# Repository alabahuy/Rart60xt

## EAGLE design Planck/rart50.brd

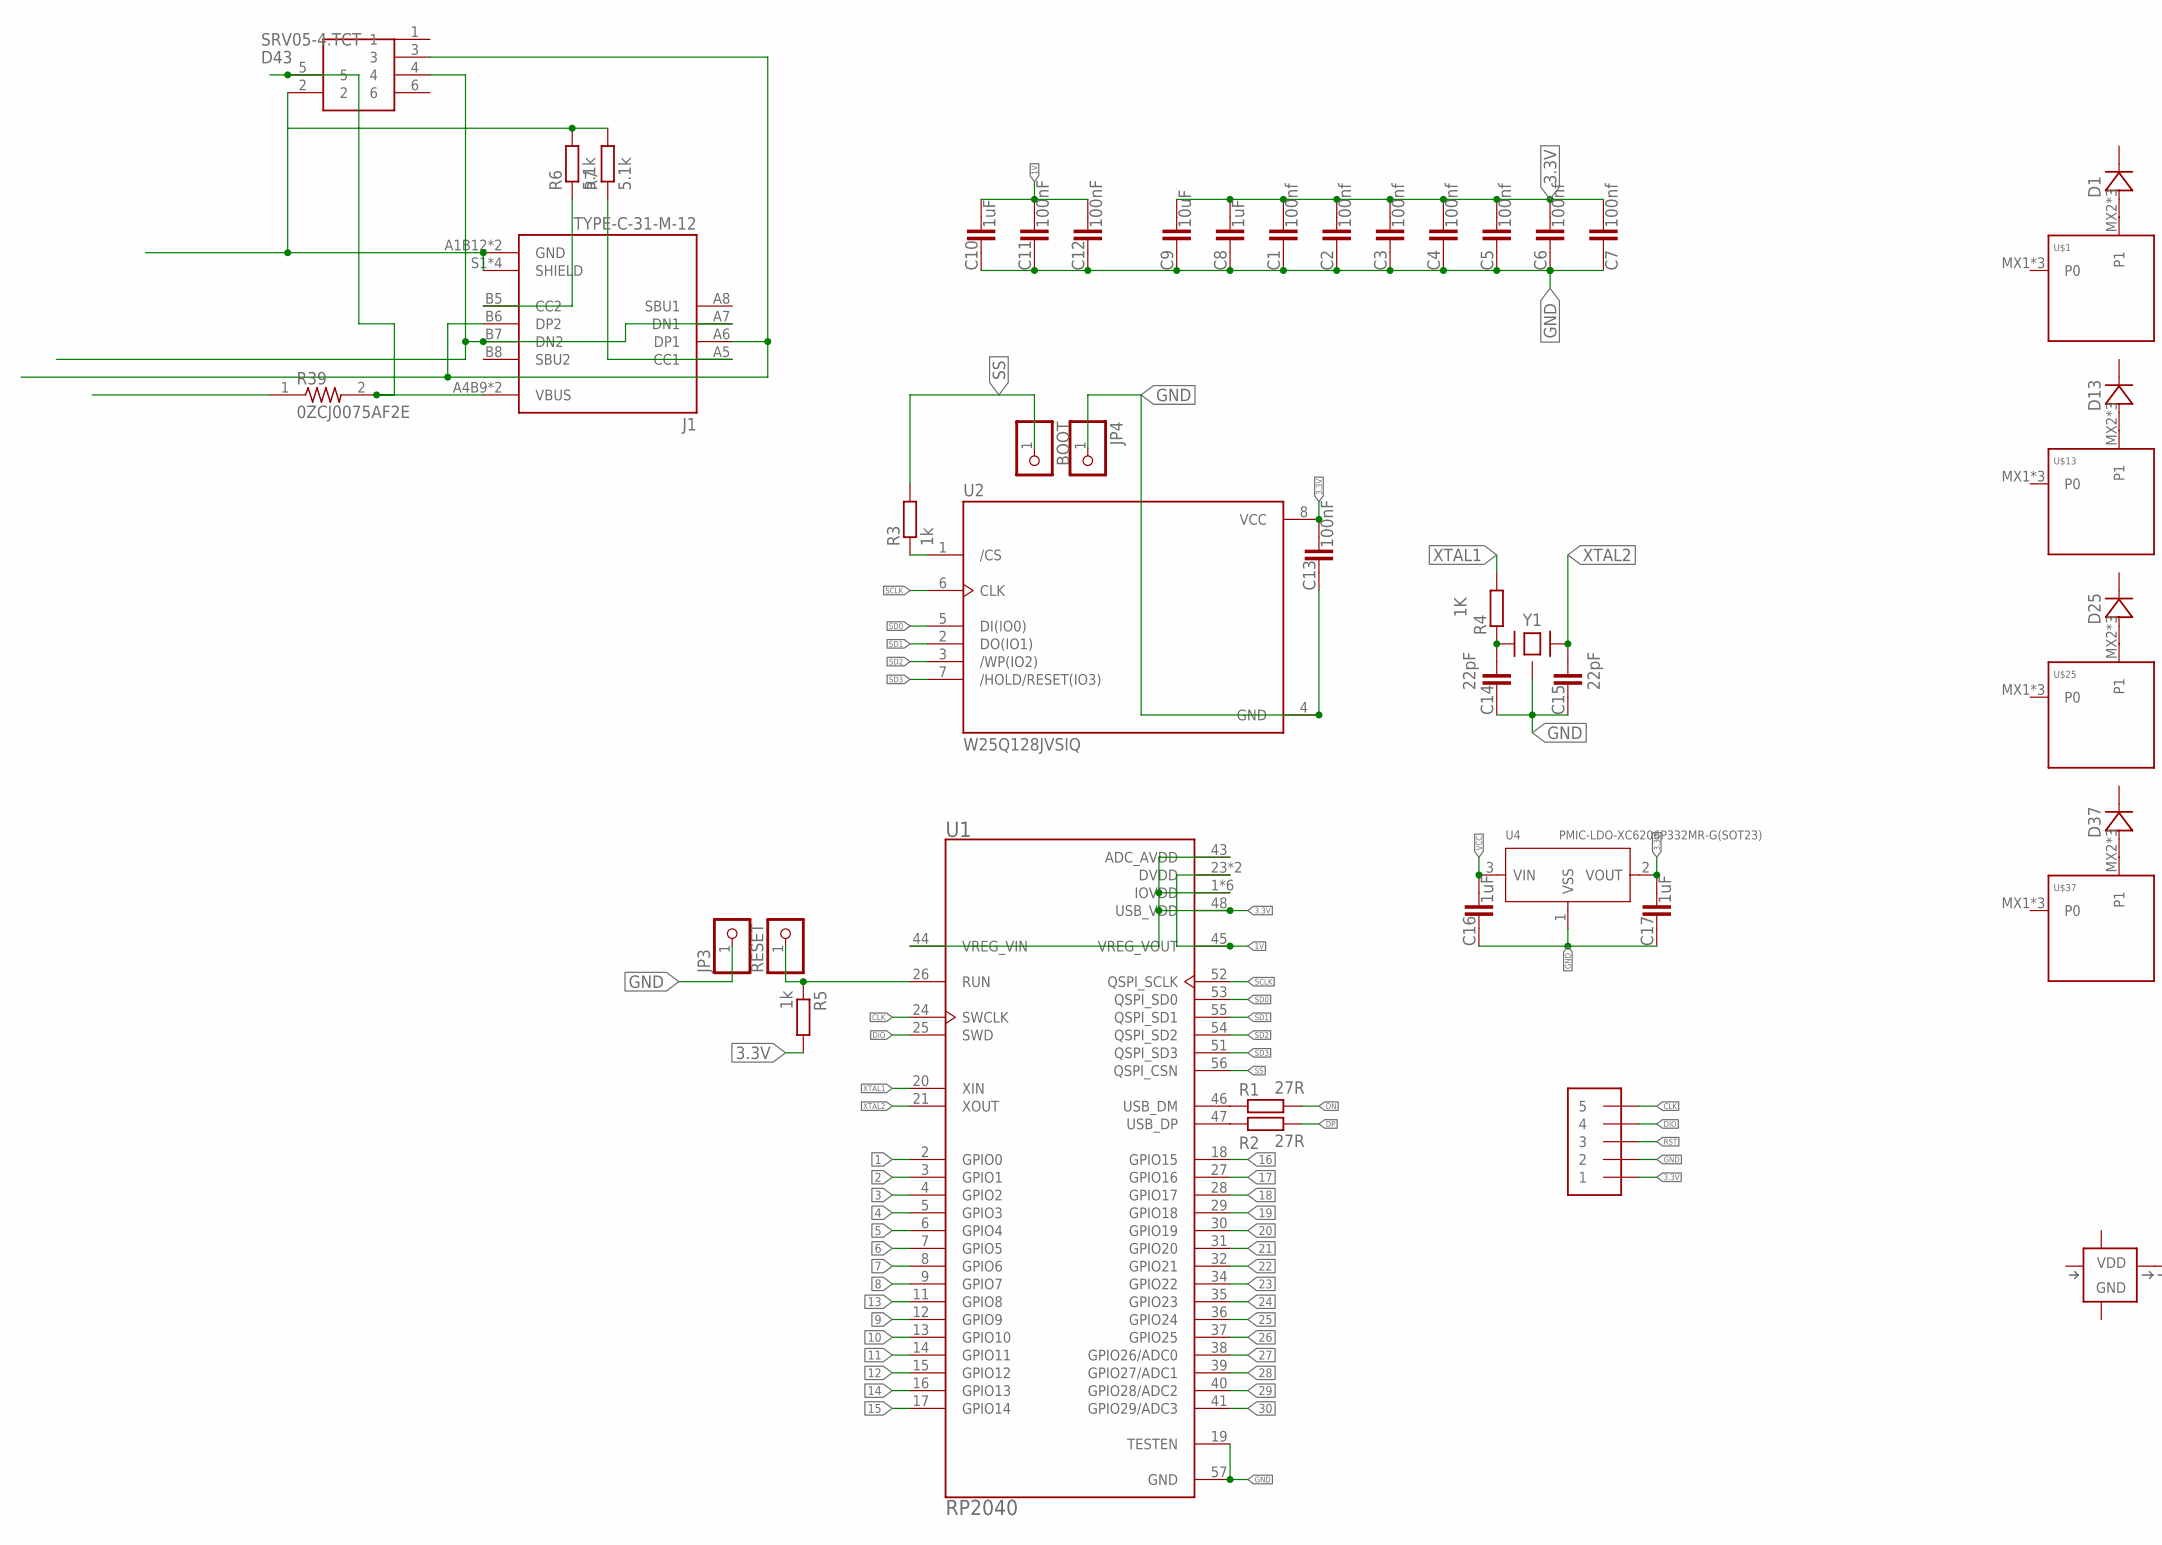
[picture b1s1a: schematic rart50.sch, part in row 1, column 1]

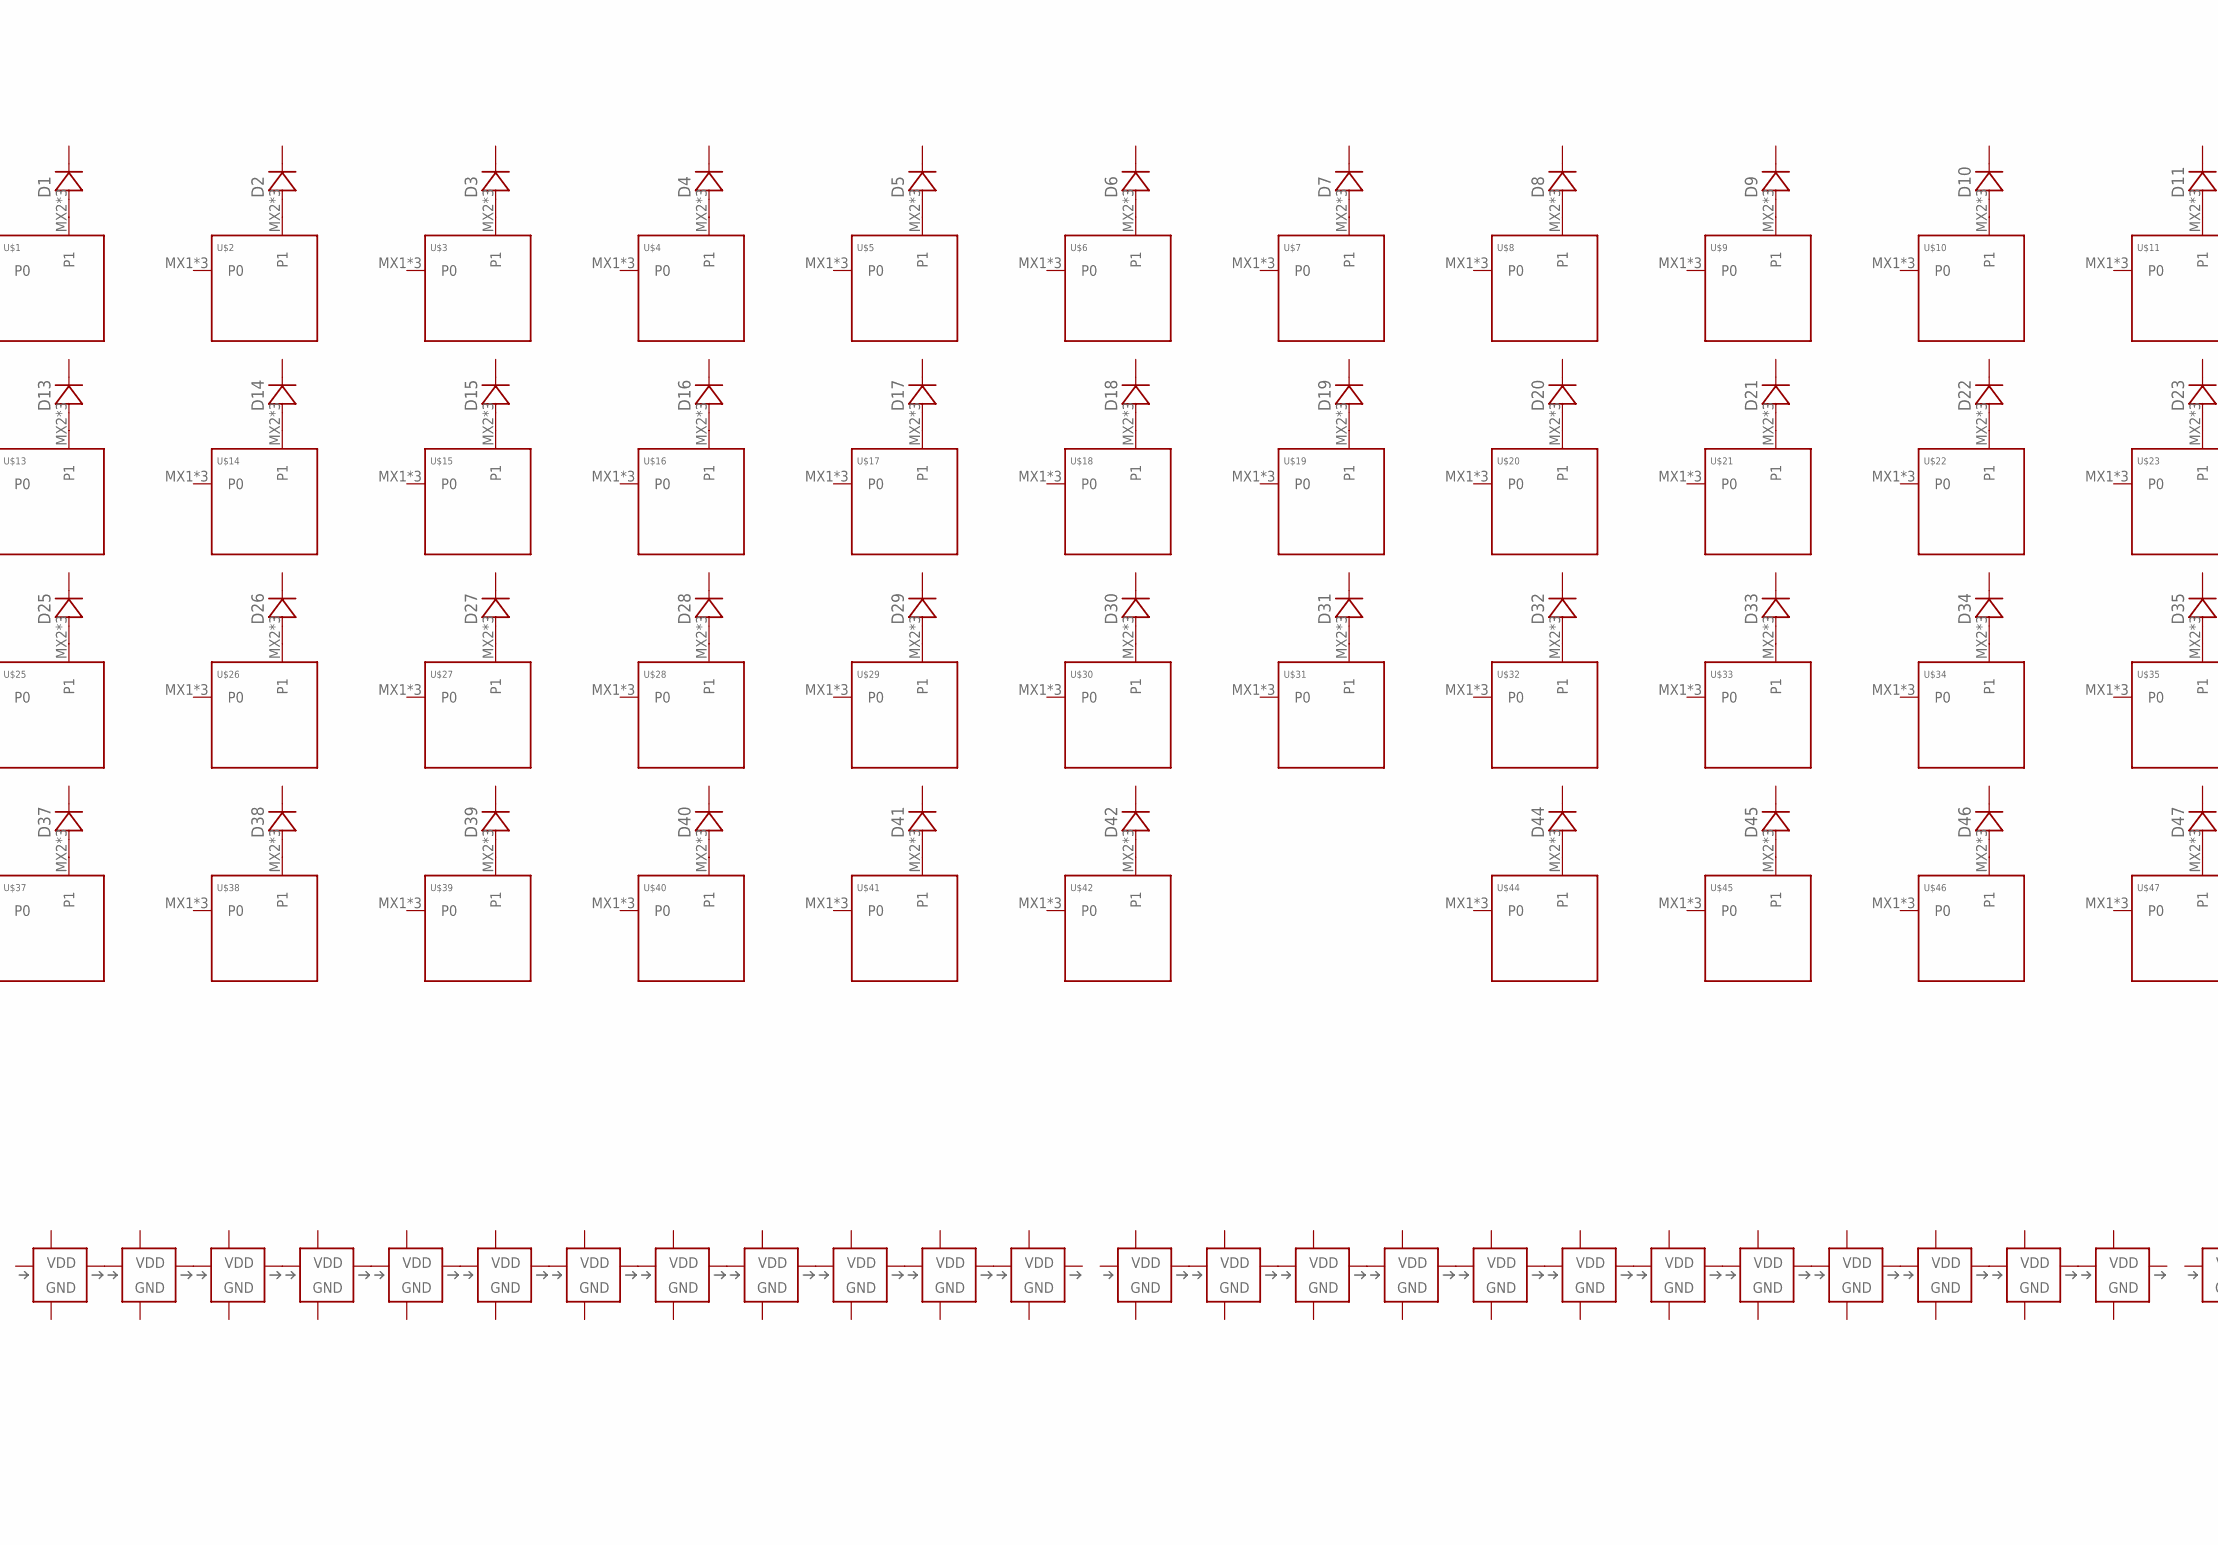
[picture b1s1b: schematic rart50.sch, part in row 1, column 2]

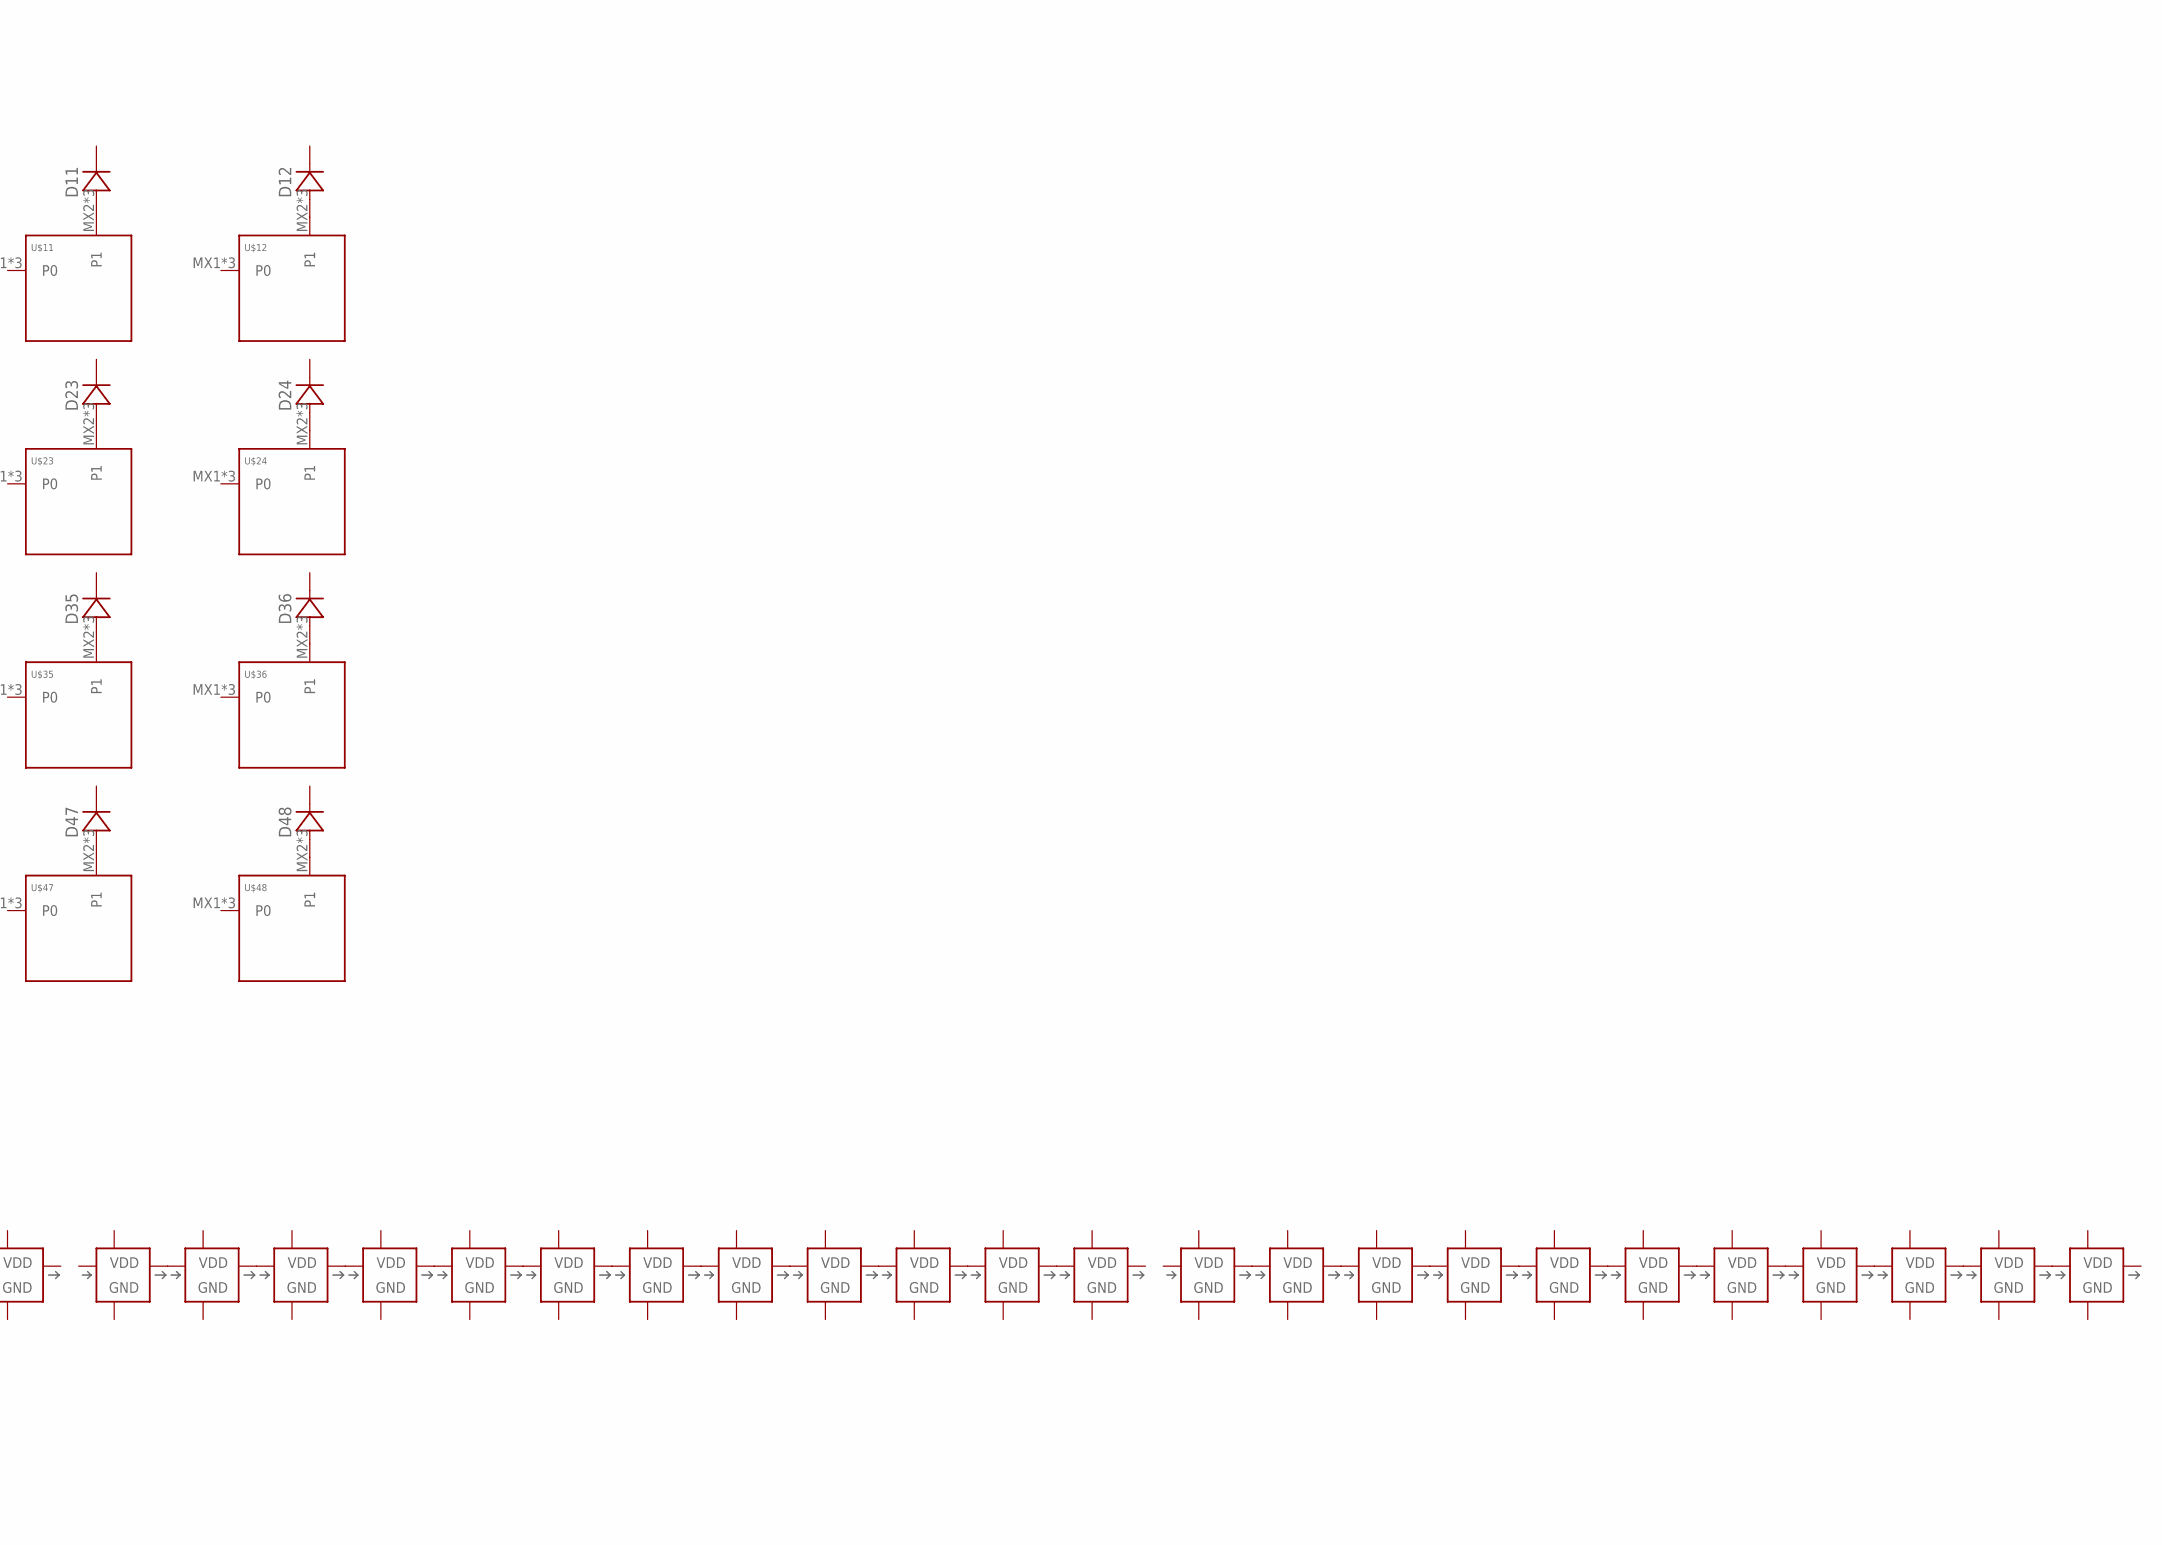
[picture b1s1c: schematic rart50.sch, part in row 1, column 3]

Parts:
BOOT: PINHD-1X1; 1X01
C1, C2, C3, C4, C5, C6, C7: 100nf; C0603
C8, C10, C16, C17: 1uF; C0603
C9: 10uF; C0603
C11, C12, C13: 100nF; C0603
C14, C15: 22pF; C0603
D1, D2, D3, D4, D5, D6, D7, D8, D9, D10, D11, D12, D13, D14, D15, D16, D17, D18, D19, D20, D21, D22, D23, D24, D25, D26, D27, D28, D29, D30, D31, D32, D33, D34, D35, D36, D37, D38, D39, D40, D41, D42, D44, D45, D46, D47, D48: DIODE-SOD-123; SOD-123
D43: SRV05-4.TCT; SOT95P280X145-6N
J1: TYPE-C-31-M-12; HRO_TYPE-C-31-M-12
J2: 1X5; 1X05-3.5MM
JP3, JP4: PINHD-1X1CB; 1X01-CLEANBIG
R1, R2: 27R; R0603
R3, R5: 1k; R0603
R4: 1K; R0603
R6, R7: 5.1k; R0603
R39: 0ZCJ0075AF2E; RESC3216X125N
RESET: PINHD-1X1; 1X01
U1: RP2040; QFN40P700X700X90-57N
U2: W25Q128JVSIQ; SOIC127P790X216-8N
U4: PMIC-LDO-XC6206P332MR-G(SOT23); SOT-23
U$1, U$2, U$3, U$4, U$5, U$6, U$7, U$8, U$9, U$10, U$11, U$12, U$13, U$14, U$15, U$16, U$17, U$18, U$19, U$20, U$21, U$22, U$23, U$24, U$25, U$26, U$27, U$28, U$29, U$30, U$31, U$32, U$33, U$34, U$35, U$36, U$37, U$38, U$39, U$40, U$41, U$44, U$45, U$46, U$47, U$48: KEYSWITCH-PLAIN-MXHSPCB-1U; MXHSPCB-1U
U$42: KEYSWITCH-PLAIN-MXHSPCB-2U-FLIPPED; MXHSPCB-2U-FLIPPED
U$43, U$49, U$50, U$51, U$52, U$53, U$54, U$55, U$56, U$57, U$58, U$59, U$60, U$61, U$62, U$63, U$64, U$65, U$66, U$67, U$68, U$69, U$70, U$71, U$72, U$73, U$74, U$75, U$76, U$77, U$78, U$79, U$80, U$81, U$82, U$83, U$84, U$85, U$86, U$87, U$88, U$89, U$90, U$91, U$92, U$93, U$94: SK6812MINI; LED-3535
Y1: CRYSTAL-4PIN-3.2X2.5; CRYSTAL-3.2X2.5

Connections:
1: U1.2 (GPIO0)
1V: C10.2, C11.2, C12.2, U1.23 (DVDD), U1.45 (VREG_VOUT), U1.50 (DVDD)
2: U1.3 (GPIO1)
3: U1.4 (GPIO2)
3.3V: C1.2, C2.2, C3.2, C4.2, C5.2, C6.2, C7.2, C8.2, C9.2, C13.2, C17.2, J2.1, R5.2, U1.1 (IOVDD), U1.10 (IOVDD), U1.22 (IOVDD), U1.33 (IOVDD), U1.42 (IOVDD), U1.43 (ADC_AVDD), U1.44 (VREG_VIN), U1.48 (USB_VDD), U1.49 (IOVDD), U2.8 (VCC), U4.2 (VOUT)
4: U1.5 (GPIO3)
5: U1.6 (GPIO4)
6: U1.7 (GPIO5)
7: U1.8 (GPIO6)
8: U1.9 (GPIO7)
9: U1.12 (GPIO9)
10: U1.13 (GPIO10)
11: U1.14 (GPIO11)
12: U1.15 (GPIO12)
13: U1.11 (GPIO8)
14: U1.16 (GPIO13)
15: U1.17 (GPIO14)
16: U1.18 (GPIO15)
17: U1.27 (GPIO16)
18: U1.28 (GPIO17)
19: U1.29 (GPIO18)
20: U1.30 (GPIO19)
21: U1.31 (GPIO20)
22: U1.32 (GPIO21)
23: U1.34 (GPIO22)
24: U1.35 (GPIO23)
25: U1.36 (GPIO24)
26: U1.37 (GPIO25)
27: U1.38 (GPIO26/ADC0)
28: U1.39 (GPIO27/ADC1)
29: U1.40 (GPIO28/ADC2)
30: U1.41 (GPIO29/ADC3)
CLK: J2.5, U1.24 (SWCLK)
DIO: J2.4, U1.25 (SWD)
DN: R1.2
DN-: D43.4, J1.A7 (DN1), J1.B7 (DN2)
DP: R2.2
DP+: D43.3, J1.A6 (DP1), J1.B6 (DP2)
GND: C1.1, C2.1, C3.1, C4.1, C5.1, C6.1, C7.1, C8.1, C9.1, C10.1, C11.1, C12.1, C13.1, C14.1, C15.1, C16.1, C17.1, J2.2, JP3.1, JP4.1, U1.19 (TESTEN), U1.57 (GND), U2.4 (GND), U4.1 (VSS), U$43.2 (GND), U$49.2 (GND), U$50.2 (GND), U$51.2 (GND), U$52.2 (GND), U$53.2 (GND), U$54.2 (GND), U$55.2 (GND), U$56.2 (GND), U$57.2 (GND), U$58.2 (GND), U$59.2 (GND), U$60.2 (GND), U$61.2 (GND), U$62.2 (GND), U$63.2 (GND), U$64.2 (GND), U$65.2 (GND), U$66.2 (GND), U$67.2 (GND), U$68.2 (GND), U$69.2 (GND), U$70.2 (GND), U$71.2 (GND), U$72.2 (GND), U$73.2 (GND), U$74.2 (GND), U$75.2 (GND), U$76.2 (GND), U$77.2 (GND), U$78.2 (GND), U$79.2 (GND), U$80.2 (GND), U$81.2 (GND), U$82.2 (GND), U$83.2 (GND), U$84.2 (GND), U$85.2 (GND), U$86.2 (GND), U$87.2 (GND), U$88.2 (GND), U$89.2 (GND), U$90.2 (GND), U$91.2 (GND), U$92.2 (GND), U$93.2 (GND), U$94.2 (GND), Y1.2 (GND), Y1.4 (GND)
GND1: D43.2, J1.A1B12 (GND), J1.B1A12 (GND), J1.S1 (SHIELD), J1.S2 (SHIELD), J1.S3 (SHIELD), J1.S4 (SHIELD), R6.2, R7.2
unnamed: D1.A, U$1.MX2 (P1), U$1.P$3 (P1), U$1.P$4 (P1)
unnamed: D2.A, U$2.MX2 (P1), U$2.P$3 (P1), U$2.P$4 (P1)
unnamed: D3.A, U$3.MX2 (P1), U$3.P$3 (P1), U$3.P$4 (P1)
unnamed: D4.A, U$4.MX2 (P1), U$4.P$3 (P1), U$4.P$4 (P1)
unnamed: D5.A, U$5.MX2 (P1), U$5.P$3 (P1), U$5.P$4 (P1)
unnamed: D6.A, U$6.MX2 (P1), U$6.P$3 (P1), U$6.P$4 (P1)
unnamed: D7.A, U$7.MX2 (P1), U$7.P$3 (P1), U$7.P$4 (P1)
unnamed: D8.A, U$8.MX2 (P1), U$8.P$3 (P1), U$8.P$4 (P1)
unnamed: D9.A, U$9.MX2 (P1), U$9.P$3 (P1), U$9.P$4 (P1)
unnamed: D10.A, U$10.MX2 (P1), U$10.P$3 (P1), U$10.P$4 (P1)
unnamed: D11.A, U$11.MX2 (P1), U$11.P$3 (P1), U$11.P$4 (P1)
unnamed: D12.A, U$12.MX2 (P1), U$12.P$3 (P1), U$12.P$4 (P1)
unnamed: D13.A, U$13.MX2 (P1), U$13.P$3 (P1), U$13.P$4 (P1)
unnamed: D14.A, U$14.MX2 (P1), U$14.P$3 (P1), U$14.P$4 (P1)
unnamed: D15.A, U$15.MX2 (P1), U$15.P$3 (P1), U$15.P$4 (P1)
unnamed: D16.A, U$16.MX2 (P1), U$16.P$3 (P1), U$16.P$4 (P1)
unnamed: D17.A, U$17.MX2 (P1), U$17.P$3 (P1), U$17.P$4 (P1)
unnamed: D18.A, U$18.MX2 (P1), U$18.P$3 (P1), U$18.P$4 (P1)
unnamed: D19.A, U$19.MX2 (P1), U$19.P$3 (P1), U$19.P$4 (P1)
unnamed: D20.A, U$20.MX2 (P1), U$20.P$3 (P1), U$20.P$4 (P1)
unnamed: D21.A, U$21.MX2 (P1), U$21.P$3 (P1), U$21.P$4 (P1)
unnamed: D22.A, U$22.MX2 (P1), U$22.P$3 (P1), U$22.P$4 (P1)
unnamed: D23.A, U$23.MX2 (P1), U$23.P$3 (P1), U$23.P$4 (P1)
unnamed: D24.A, U$24.MX2 (P1), U$24.P$3 (P1), U$24.P$4 (P1)
unnamed: D25.A, U$25.MX2 (P1), U$25.P$3 (P1), U$25.P$4 (P1)
unnamed: D26.A, U$26.MX2 (P1), U$26.P$3 (P1), U$26.P$4 (P1)
unnamed: D27.A, U$27.MX2 (P1), U$27.P$3 (P1), U$27.P$4 (P1)
unnamed: D28.A, U$28.MX2 (P1), U$28.P$3 (P1), U$28.P$4 (P1)
unnamed: D29.A, U$29.MX2 (P1), U$29.P$3 (P1), U$29.P$4 (P1)
unnamed: D30.A, U$30.MX2 (P1), U$30.P$3 (P1), U$30.P$4 (P1)
unnamed: D31.A, U$31.MX2 (P1), U$31.P$3 (P1), U$31.P$4 (P1)
unnamed: D32.A, U$32.MX2 (P1), U$32.P$3 (P1), U$32.P$4 (P1)
unnamed: D33.A, U$33.MX2 (P1), U$33.P$3 (P1), U$33.P$4 (P1)
unnamed: D34.A, U$34.MX2 (P1), U$34.P$3 (P1), U$34.P$4 (P1)
unnamed: D35.A, U$35.MX2 (P1), U$35.P$3 (P1), U$35.P$4 (P1)
unnamed: D36.A, U$36.MX2 (P1), U$36.P$3 (P1), U$36.P$4 (P1)
unnamed: D37.A, U$37.MX2 (P1), U$37.P$3 (P1), U$37.P$4 (P1)
unnamed: D38.A, U$38.MX2 (P1), U$38.P$3 (P1), U$38.P$4 (P1)
unnamed: D39.A, U$39.MX2 (P1), U$39.P$3 (P1), U$39.P$4 (P1)
unnamed: D40.A, U$40.MX2 (P1), U$40.P$3 (P1), U$40.P$4 (P1)
unnamed: D41.A, U$41.MX2 (P1), U$41.P$3 (P1), U$41.P$4 (P1)
unnamed: D42.A, U$42.MX2 (P1), U$42.P$3 (P1), U$42.P$4 (P1)
unnamed: D44.A, U$44.MX2 (P1), U$44.P$3 (P1), U$44.P$4 (P1)
unnamed: D45.A, U$45.MX2 (P1), U$45.P$3 (P1), U$45.P$4 (P1)
unnamed: D46.A, U$46.MX2 (P1), U$46.P$3 (P1), U$46.P$4 (P1)
unnamed: D47.A, U$47.MX2 (P1), U$47.P$3 (P1), U$47.P$4 (P1)
unnamed: D48.A, U$48.MX2 (P1), U$48.P$3 (P1), U$48.P$4 (P1)
unnamed: U$43.3 (DO), U$49.1 (DI)
unnamed: U$49.3 (DO), U$50.1 (DI)
unnamed: U$50.3 (DO), U$51.1 (DI)
unnamed: U$51.3 (DO), U$52.1 (DI)
unnamed: U$52.3 (DO), U$53.1 (DI)
unnamed: U$53.3 (DO), U$54.1 (DI)
unnamed: U$54.3 (DO), U$55.1 (DI)
unnamed: U$55.3 (DO), U$56.1 (DI)
unnamed: U$56.3 (DO), U$57.1 (DI)
unnamed: U$57.3 (DO), U$58.1 (DI)
unnamed: U$58.3 (DO), U$59.1 (DI)
unnamed: U$60.3 (DO), U$61.1 (DI)
unnamed: U$61.3 (DO), U$62.1 (DI)
unnamed: U$62.3 (DO), U$63.1 (DI)
unnamed: U$63.3 (DO), U$64.1 (DI)
unnamed: U$64.3 (DO), U$65.1 (DI)
unnamed: U$65.3 (DO), U$66.1 (DI)
unnamed: U$66.3 (DO), U$67.1 (DI)
unnamed: U$67.3 (DO), U$68.1 (DI)
unnamed: U$68.3 (DO), U$69.1 (DI)
unnamed: U$69.3 (DO), U$70.1 (DI)
unnamed: U$70.3 (DO), U$71.1 (DI)
unnamed: U$72.3 (DO), U$73.1 (DI)
unnamed: U$73.3 (DO), U$74.1 (DI)
unnamed: U$74.3 (DO), U$75.1 (DI)
unnamed: U$75.3 (DO), U$76.1 (DI)
unnamed: U$76.3 (DO), U$77.1 (DI)
unnamed: U$77.3 (DO), U$78.1 (DI)
unnamed: U$78.3 (DO), U$79.1 (DI)
unnamed: U$79.3 (DO), U$80.1 (DI)
unnamed: U$80.3 (DO), U$81.1 (DI)
unnamed: U$81.3 (DO), U$82.1 (DI)
unnamed: U$82.3 (DO), U$83.1 (DI)
unnamed: U$84.3 (DO), U$85.1 (DI)
unnamed: U$85.3 (DO), U$86.1 (DI)
unnamed: U$86.3 (DO), U$87.1 (DI)
unnamed: U$87.3 (DO), U$88.1 (DI)
unnamed: U$88.3 (DO), U$89.1 (DI)
unnamed: U$89.3 (DO), U$90.1 (DI)
unnamed: U$90.3 (DO), U$91.1 (DI)
unnamed: U$91.3 (DO), U$92.1 (DI)
unnamed: U$92.3 (DO), U$93.1 (DI)
unnamed: U$93.3 (DO), U$94.1 (DI)
unnamed: R1.1, U1.46 (USB_DM)
unnamed: R2.1, U1.47 (USB_DP)
unnamed: C14.2, R4.1, Y1.1
unnamed: R3.1, U2.1 (/CS)
unnamed: D43.5, J1.A4B9 (VBUS), J1.B4A9 (VBUS), R39.2
unnamed: J1.B5 (CC2), R6.1
unnamed: J1.A5 (CC1), R7.1
RST: J2.3, R5.1, RESET.1, U1.26 (RUN)
SCLK: U1.52 (QSPI_SCLK), U2.6 (CLK)
SD0: U1.53 (QSPI_SD0), U2.5 (DI(IO0))
SD1: U1.55 (QSPI_SD1), U2.2 (DO(IO1))
SD2: U1.54 (QSPI_SD2), U2.3 (/WP(IO2))
SD3: U1.51 (QSPI_SD3), U2.7 (/HOLD/RESET(IO3))
SS: BOOT.1, R3.2, U1.56 (QSPI_CSN)
VCC: C16.2, U4.3 (VIN)
VCC1: R39.1
VDD: U$43.4 (VDD), U$49.4 (VDD), U$50.4 (VDD), U$51.4 (VDD), U$52.4 (VDD), U$53.4 (VDD), U$54.4 (VDD), U$55.4 (VDD), U$56.4 (VDD), U$57.4 (VDD), U$58.4 (VDD), U$59.4 (VDD), U$60.4 (VDD), U$61.4 (VDD), U$62.4 (VDD), U$63.4 (VDD), U$64.4 (VDD), U$65.4 (VDD), U$66.4 (VDD), U$67.4 (VDD), U$68.4 (VDD), U$69.4 (VDD), U$70.4 (VDD), U$71.4 (VDD), U$72.4 (VDD), U$73.4 (VDD), U$74.4 (VDD), U$75.4 (VDD), U$76.4 (VDD), U$77.4 (VDD), U$78.4 (VDD), U$79.4 (VDD), U$80.4 (VDD), U$81.4 (VDD), U$82.4 (VDD), U$83.4 (VDD), U$84.4 (VDD), U$85.4 (VDD), U$86.4 (VDD), U$87.4 (VDD), U$88.4 (VDD), U$89.4 (VDD), U$90.4 (VDD), U$91.4 (VDD), U$92.4 (VDD), U$93.4 (VDD), U$94.4 (VDD)
XTAL1: R4.2, U1.20 (XIN)
XTAL2: C15.2, U1.21 (XOUT), Y1.3 (2)

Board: 2 copper layers, 177 parts (157 on the bottom side), 116 nets, no tracks yet.

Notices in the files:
parts and their libraries:
SparkFun-Switches: Licensing: Creative Commons ShareAlike 4.0 International - https://creativecommons.org/licenses/by-sa/4.0
